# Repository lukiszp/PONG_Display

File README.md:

# PONG_Display

Its project of RGB display. Using ping pong balls, RGB diodes and WiFi module.

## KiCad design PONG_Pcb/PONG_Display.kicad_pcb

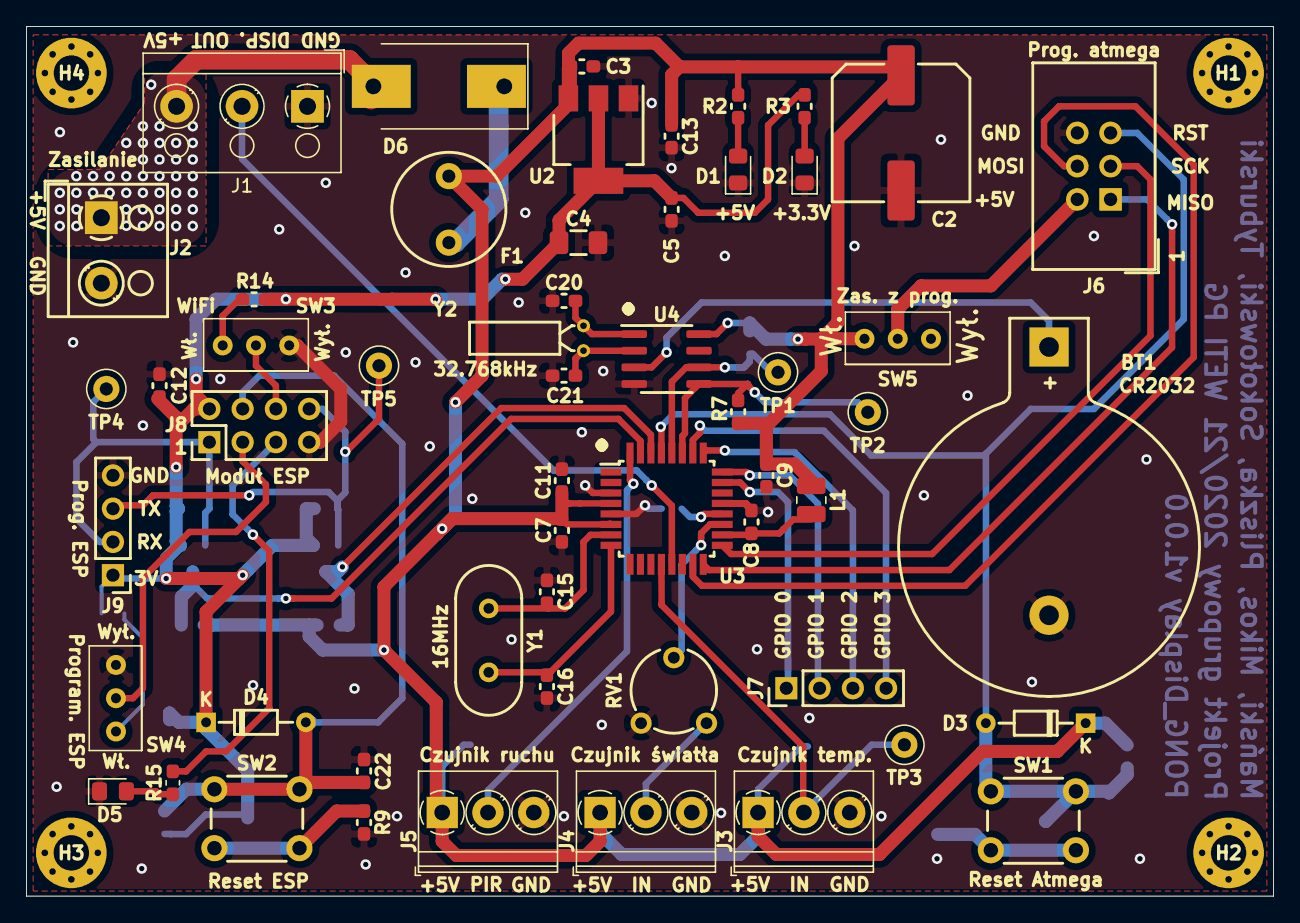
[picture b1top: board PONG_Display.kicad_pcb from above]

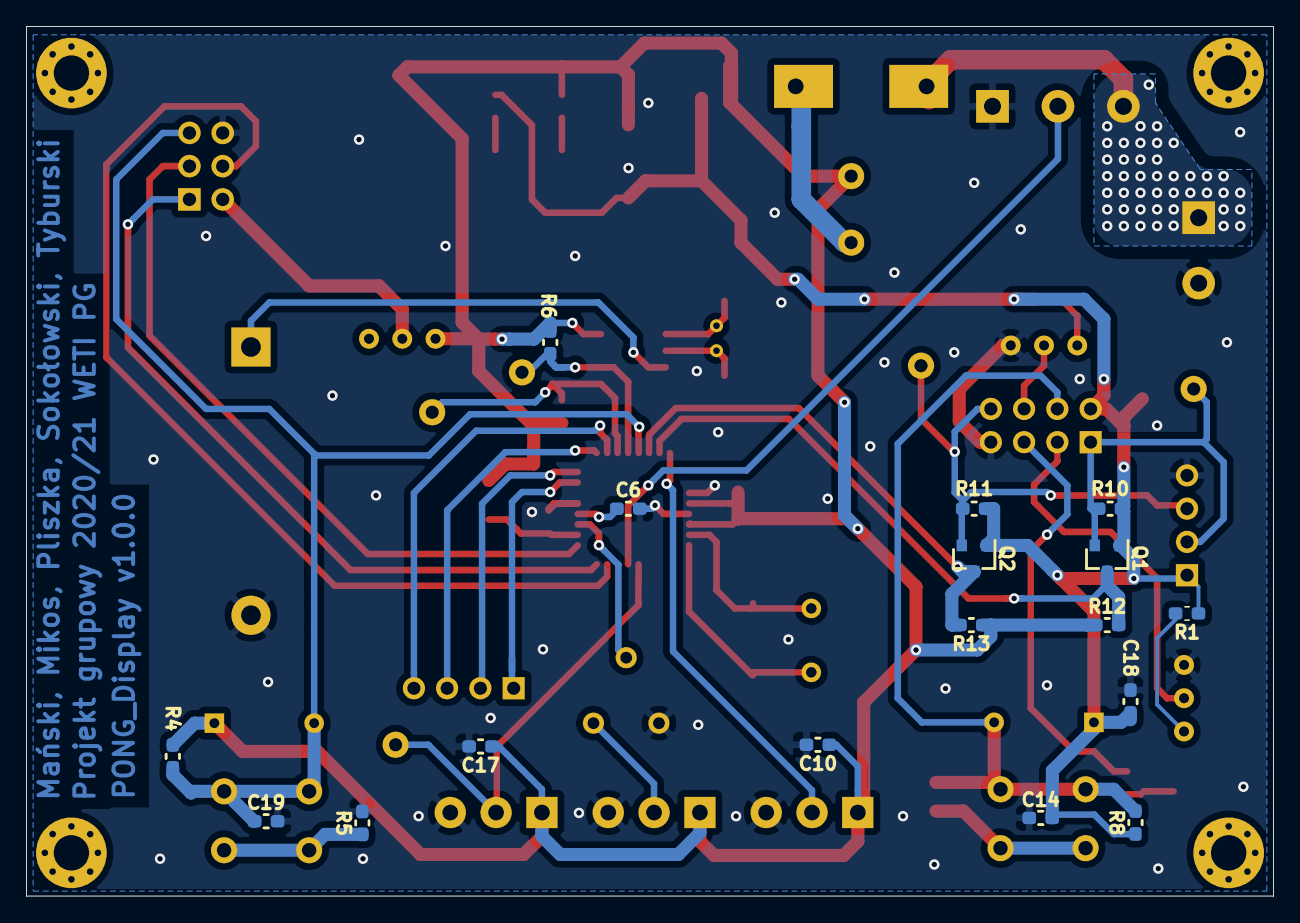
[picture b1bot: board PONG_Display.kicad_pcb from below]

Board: 2 copper layers, 95.2 x 66.4 mm, 76 parts (17 on the bottom side), 43 nets.

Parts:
BT1: Battery_Cell; BatteryHolder_Keystone_103_1x20mm
C2: 470u; C_Elec_10x10.2
C3, C5, C6, C7, C8, C9, C10, C11, C12, C13, C14, C17, C18, C19, C22: 100n; C_0603_1608Metric_Pad1.05x0.95mm_HandSolder
C4: 10u; C_1206_3216Metric_Pad1.42x1.75mm_HandSolder
C15, C16, C20, C21: 22p; C_0603_1608Metric_Pad1.05x0.95mm_HandSolder
D1: RED_LED; D_0805_2012Metric_Pad1.15x1.40mm_HandSolder
D2: GREEN_LED; D_0805_2012Metric_Pad1.15x1.40mm_HandSolder
D3, D4: D_Zener; D_DO-34_SOD68_P7.62mm_Horizontal
D5: BLUE_LED; D_0805_2012Metric_Pad1.15x1.40mm_HandSolder
D6: 1N4001; D_SMC-RM10_Universal_Handsoldering
F1: Fuse; Fuse_Littelfuse_372_D8.50mm
H1, H2, H3, H4: MountingHole; MountingHole_2.7mm_Pad_Via
J1: LED_Display_Conn; TerminalBlock_RND_205-00002_1x03_P5.00mm_Horizontal
J2: Input_Supply+5V; TerminalBlock_RND_205-00001_1x02_P5.00mm_Horizontal
J3: DHT22_Conn; TerminalBlock_Phoenix_PT-1,5-3-3.5-H_1x03_P3.50mm_Horizontal
J4: LightSensor_Conn; TerminalBlock_Phoenix_PT-1,5-3-3.5-H_1x03_P3.50mm_Horizontal
J5: PIR_Sensor_Conn; TerminalBlock_Phoenix_PT-1,5-3-3.5-H_1x03_P3.50mm_Horizontal
J6: AVR-ISP-6; IDC-Header_2x03_P2.54mm_Vertical
J7: Conn_01x04; PinHeader_1x04_P2.54mm_Vertical
J8: ESP_Conn; PinHeader_2x04_P2.54mm_Vertical
J9: ESP_Prog_Conn; PinHeader_1x04_P2.54mm_Vertical
L1: 10u; L_1008_2520Metric
Q1, Q2: BSS138; SOT-23
R1, R4, R6, R7, R8, R10, R11, R12, R13, R14: 10k; R_0603_1608Metric_Pad1.05x0.95mm_HandSolder
R2: 470R; R_0603_1608Metric_Pad1.05x0.95mm_HandSolder
R3, R5, R9, R15: 330R; R_0603_1608Metric_Pad1.05x0.95mm_HandSolder
RV1: R_POT; Potentiometer_Piher_PT-6-V_Vertical
SW1, SW2: SW_Push; SW_PUSH_6mm
SW3, SW4, SW5: SW_Push_SPDT; SPDT_switch
TP1, TP2, TP3, TP4, TP5: TestPoint; TestPoint_Loop_D1.80mm_Drill1.0mm_Beaded
U2: LD1117S33TR_SOT223; SOT-223-3_TabPin2
U3: ATmega328P-AU; TQFP-32_7x7mm_P0.8mm
U4: MCP79400; SOIC-8_3.9x4.9mm_P1.27mm
Y1: 16MHz; Crystal_HC49-4H_Vertical
Y2: 32,768kHz; Crystal_C26-LF_D2.1mm_L6.5mm_Horizontal

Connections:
+3V3: C4.1, C5.1, C12.1, C14.1, C18.1, D4.1, J8.2, J9.1, Q1.1, Q2.1, R1.1, R3.1, R8.1, R10.1, R11.1, R14.1, U2.2
+5V: C2.1, C3.1, C7.1, C9.1, C10.1, C11.1, C13.1, C17.1, D3.1, F1.1, J3.1, J4.1, J5.1, L1.2, R2.1, R4.1, R6.1, R7.1, R12.1, R13.1, SW5.1, U2.3, U3.4, U3.6, U4.8
+5VA: D6.2, J1.3, J2.1
/MikrokontrolerAtmega/DHT22_DATA: J3.2, TP3.1, U3.12
/MikrokontrolerAtmega/ESP_RX_HIGH: Q1.3, R12.2, U3.31
/MikrokontrolerAtmega/ESP_TX_HIGH: Q2.3, R13.2, U3.30
/MikrokontrolerAtmega/LED_DATA: J1.2, U3.13
/MikrokontrolerAtmega/LIGHT_SENSOR_OUT: J4.2, RV1.1
/MikrokontrolerAtmega/RTC_SCL: R6.2, TP1.1, U3.28, U4.6
/MikrokontrolerAtmega/RTC_SDA: R7.2, TP2.1, U3.27, U4.5
/MikrokontrolerAtmega/uC_GPIO0: J7.1, U3.23
/MikrokontrolerAtmega/uC_GPIO1: J7.2, U3.24
/MikrokontrolerAtmega/uC_GPIO2: J7.3, U3.25
/MikrokontrolerAtmega/uC_GPIO3: J7.4, U3.26
/MikrokontrolerAtmega/uC_MISO: J6.1, U3.16
/MikrokontrolerAtmega/uC_MOSI: J6.4, U3.15
/MikrokontrolerAtmega/uC_RST: C19.1, D3.2, J6.5, R4.2, SW1.1, U3.29
/MikrokontrolerAtmega/uC_SCK: J6.3, U3.17
/Moduł WiFi/ESP_CH_PD: J8.6, SW3.2
/Moduł WiFi/ESP_GPIO0: J8.3, SW4.2
/Moduł WiFi/ESP_GPIO2: J8.5, R15.2
/Moduł WiFi/ESP_RST: C22.1, D4.2, J8.4, R8.2, SW2.1
/Moduł WiFi/ESP_RX: J8.1, J9.2, Q1.2, R10.2, TP4.1
/Moduł WiFi/ESP_TX: J8.8, J9.3, Q2.2, R11.2, TP5.1
/Sensory/PIR_OUT: J5.2, U3.32
GND: BT1.2, C2.2, C3.2, C4.2, C5.2, C6.2, C7.2, C8.2, C9.2, C10.2, C11.2, C12.2, C13.2, C14.2, C15.1, C16.2, C17.2, C18.2, C19.2, C20.1, C21.2, C22.2, D1.1, D2.1, D5.1, J1.1, J2.2, J3.3, J4.3, J5.3, J6.6, J8.7, J9.4, R5.2, R9.2, RV1.3, SW3.3, SW4.3, U2.1, U3.3, U3.5, U3.21, U4.4
unnamed: BT1.1, U4.3
unnamed: C6.1, U3.20
unnamed: C8.1, L1.1, U3.18
unnamed: C15.2, U3.7, Y1.1
unnamed: C16.1, U3.8, Y1.2
unnamed: C20.2, U4.1, Y2.1
unnamed: C21.1, U4.2, Y2.2
unnamed: D1.2, R2.2
unnamed: D2.2, R3.2
unnamed: D5.2, R15.1
unnamed: D6.1, F1.2
unnamed: J6.2, SW5.2
unnamed: R1.2, SW4.1
unnamed: R5.1, SW1.2
unnamed: R9.1, SW2.2
unnamed: R14.2, SW3.1
unnamed: RV1.2, U3.19

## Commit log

2020-03-29 Utworzenie projektu w KiCad
2020-03-29 Hierarchia schematów
2020-03-29 PONG_Disp
2020-03-31 Dodane footprinty
2020-04-04 napisałem coś
2020-04-04 poprawka
2020-04-04 test brancha
2020-04-04 nowe
2020-04-15 Drobne zmiany
2020-04-18 Zmiany
2020-04-18 Zmiana
2020-04-18 Zmianaa
2020-04-18 Teraz jest sexy
2020-04-18 foot
2020-04-18 po obgadaniu
2020-04-19 jeszcze do przekminienia
2020-04-19 wywalone rezystory
2020-04-19 wybrane 5V
2020-04-19 Update PONG_Display.pro
    cos
2020-04-19 dodalem rezystory i wywalilem ze zlacza zasilanie tasmy
2020-04-21 layout v1
2020-04-22 layout2
2020-04-24 layout3
2020-04-24 Updated GPIO pins in ESP schematic
    Connected GPIO2 to VDD with pull-up resistor and changed switches wiring
2020-04-25 layout4
2020-04-25 layout5
2020-04-26 laayout6
2020-04-27 layout7
2020-04-29 layout8
2020-05-01 layout9
2020-05-03 Layout 9
2020-05-03 layout 10
2020-05-03 layout11
2020-05-03 Layout 11
2020-05-03 layout 12
2020-05-13 Repo reorganized
    Reorganizacja struktury katalogów repozytorium
2020-05-13 Archiwizacja
2020-05-13 Drobne poprawki
2020-05-17 Pliki produkcyjne
2020-05-18 Poprawki layoutu
2020-05-18 Poprawki
2020-05-18 Drobne
2020-05-20 Ostatnia wersja
2020-05-26 Drobna zmiana wartości elementów
2021-01-23 poprawki koncowe
2021-01-23 stepy
2021-01-23 App main functionality
2021-01-23 Added software files
    Pong_ATmega - main functionality
    Pong_EEPROM - save fonts in EEPROM for further use
2021-01-23 Added software files
    Pong_ESP - wireless communication
